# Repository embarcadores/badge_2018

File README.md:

= Crachá 2018 =

Proposta inicial

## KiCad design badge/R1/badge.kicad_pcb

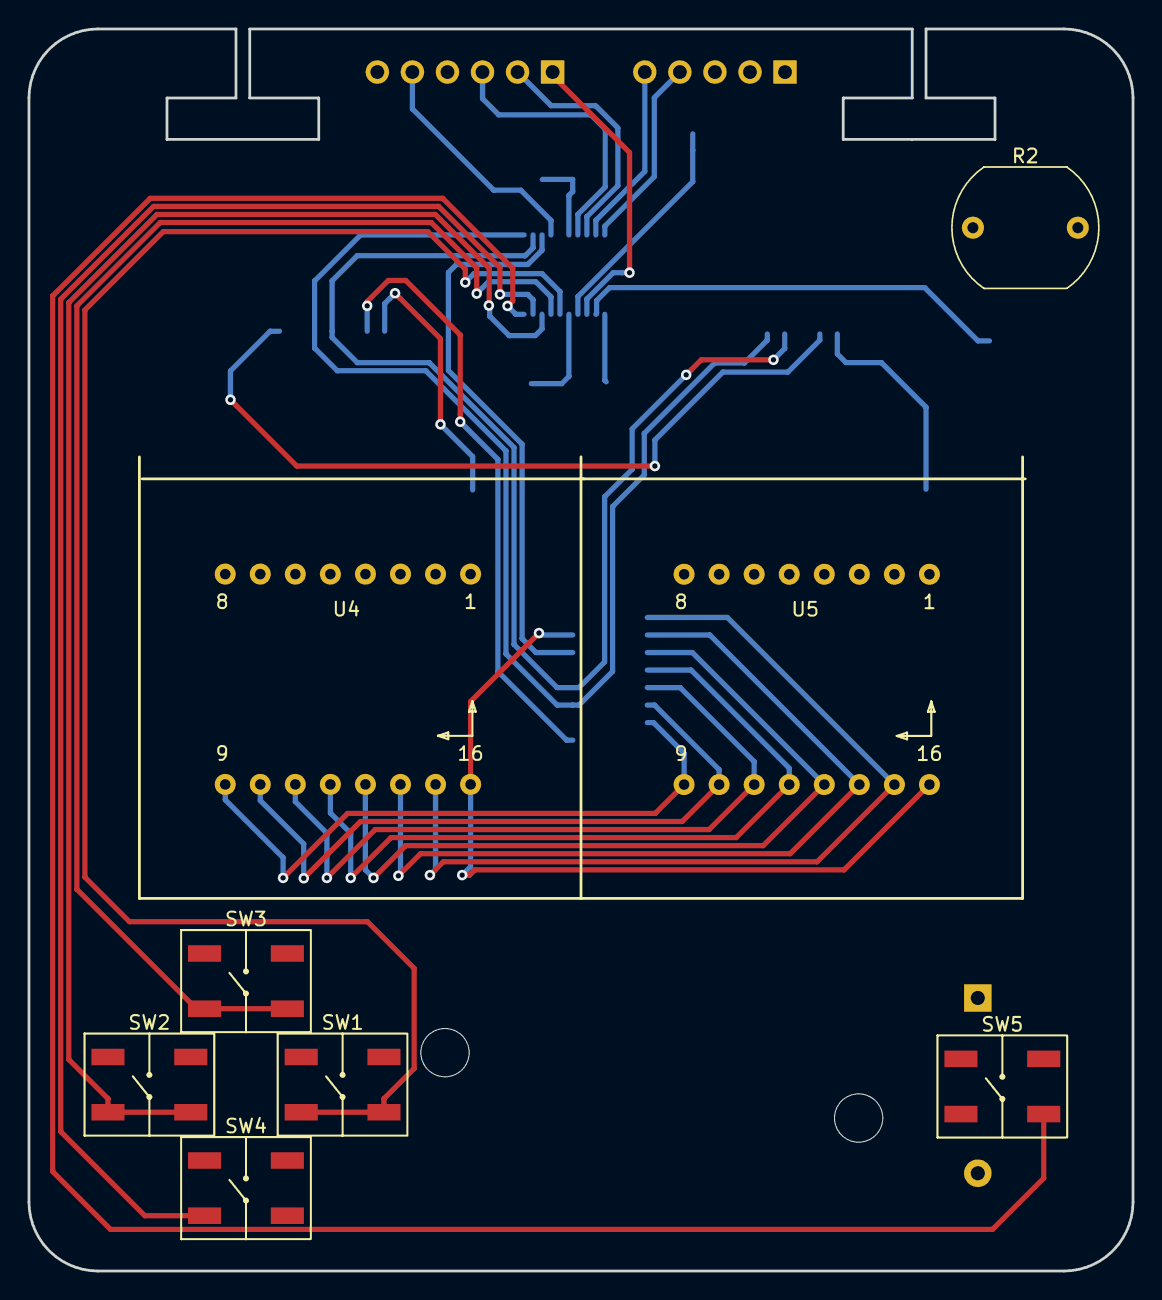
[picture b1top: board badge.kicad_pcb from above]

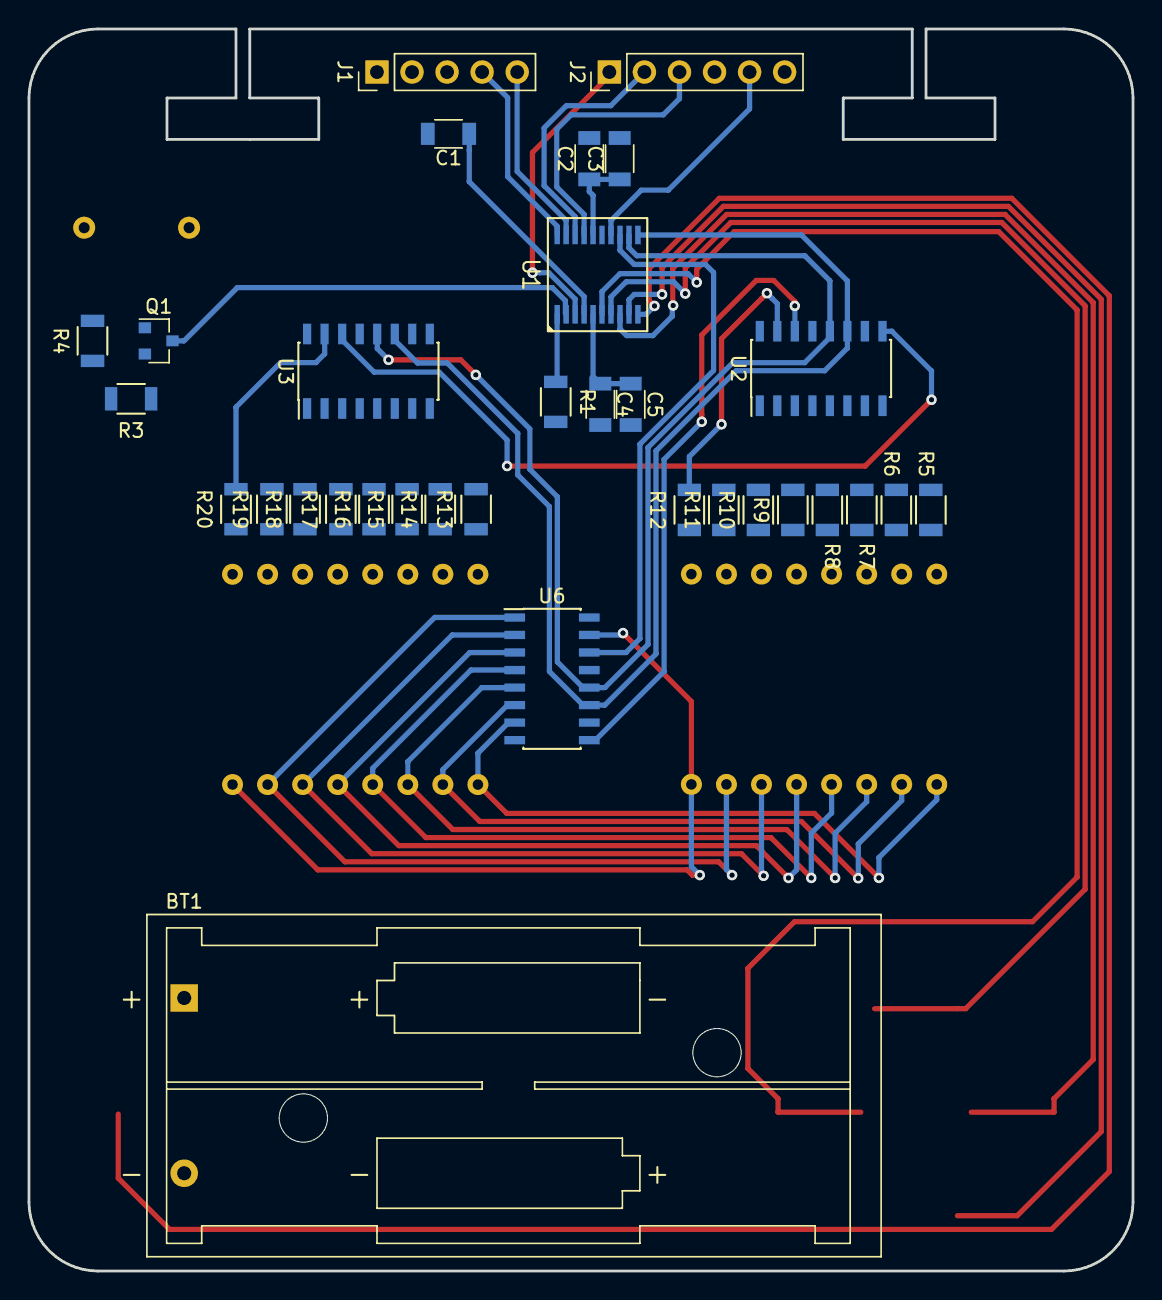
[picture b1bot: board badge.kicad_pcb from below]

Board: 2 copper layers, 80.0 x 90.0 mm, 40 parts (32 on the bottom side), 62 nets.

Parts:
BT1: AA; Keystone_2468_2xAAA
C1, C2: 100nF; C_1206
C3: 4.7uF; C_1206
C4: 10nF; C_1206
C5: 1uF; C_1206
J1: SWD; Pin_Header_Straight_1x05_Pitch2.54mm
J2: Conn_01x06; Pin_Header_Straight_1x06_Pitch2.54mm
Q1: NMOS_GSD; SOT-23
R1: 10K; R_1206_CUSTOM
R2: LDR03; Resistor_LDR_10x8.5_RM7.6
R3: 4k7; R_1206_CUSTOM
R4: 200R; R_1206_CUSTOM
R5, R6, R7, R8, R9, R10, R11, R12, R13, R14, R15, R16, R17, R18, R19, R20: 330R; R_1206_CUSTOM
SW1, SW2, SW3, SW4, SW5: SW_SPST; EVQ-Q2B02W
U1: STM32F030F4; TSOP-20-STM32F030F4
U2, U3, U6: 74HC595; SOIC-16_3.9x9.9mm_Pitch1.27mm
U4, U5: LEDMX; LED_8x8_1.9MM_20x20MM_Horiz

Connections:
/GPIO0: J2.1, U1.3
/HOLD: U1.12, U2.12, U3.12, U6.12
/MOSI: U1.13, U6.14
/NRST: C1.1, J1.3, U1.4
/RXD: Q1.3, R3.1, U1.2
/SCK: U1.11, U2.11, U3.11, U6.11
/SWCLK: J1.5, U1.19
/SWDIO: J1.4, U1.20
/SWDOWN: SW4.2, U1.9
/SWLEFT: SW2.2, U1.8
/SWMENU: SW5.2, U1.10
/SWRIGHT: SW1.2, U1.6
/SWTOP: SW3.2, U1.7
/UART_RX: J2.2, U1.18
/UART_TX: J2.3, U1.17
GND: BT1.2, C1.2, C2.2, C3.2, C4.2, C5.2, J1.2, J2.6, Q1.2, R1.2, R4.1, SW1.1, SW2.1, SW3.1, SW4.1, SW5.1, U1.15, U2.8, U2.13, U3.8, U3.13, U6.8, U6.13
unnamed: J2.5, U1.14
unnamed: Q1.1, R2.2, R4.2
unnamed: R1.1, U1.1
unnamed: R5.1, U4.8
unnamed: R5.2, U2.7
unnamed: R6.1, U4.7
unnamed: R6.2, U2.6
unnamed: R7.1, U4.6
unnamed: R7.2, U2.5
unnamed: R8.1, U4.5
unnamed: R8.2, U2.4
unnamed: R9.1, U4.4
unnamed: R9.2, U2.3
unnamed: R10.1, U4.3
unnamed: R10.2, U2.2
unnamed: R11.1, U4.2
unnamed: R11.2, U2.1
unnamed: R12.1, U4.1
unnamed: R12.2, U2.15
unnamed: R13.1, U5.8
unnamed: R13.2, U3.7
unnamed: R14.1, U5.7
unnamed: R14.2, U3.6
unnamed: R15.1, U5.6
unnamed: R15.2, U3.5
unnamed: R16.1, U5.5
unnamed: R16.2, U3.4
unnamed: R17.1, U5.4
unnamed: R17.2, U3.3
unnamed: R18.1, U5.3
unnamed: R18.2, U3.2
unnamed: R19.1, U5.2
unnamed: R19.2, U3.1
unnamed: R20.1, U5.1
unnamed: R20.2, U3.15
unnamed: U2.9, U3.14
unnamed: U2.14, U6.9
unnamed: U4.9, U5.9, U6.7
unnamed: U4.10, U5.10, U6.6
unnamed: U4.11, U5.11, U6.5
unnamed: U4.12, U5.12, U6.4
unnamed: U4.13, U5.13, U6.3
unnamed: U4.14, U5.14, U6.2
unnamed: U4.15, U5.15, U6.1
unnamed: U4.16, U5.16, U6.15
VCC: BT1.1, C2.1, C3.1, C4.1, C5.1, J1.1, J2.4, R2.1, R3.2, U1.5, U1.16, U2.10, U2.16, U3.10, U3.16, U6.10, U6.16

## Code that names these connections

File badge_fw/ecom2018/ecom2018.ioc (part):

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Mcu.Name=STM32F030F4Px
Mcu.Package=TSSOP20
Mcu.UserName=STM32F030F4Px
PA0.GPIOParameters=GPIO_Label
PA0.GPIO_Label=SWRIGHT
PA0.Signal=GPIO_Output
PA1.GPIOParameters=GPIO_Label
PA1.GPIO_Label=SWLEFT
PA1.Signal=GPIO_Output
PA10.GPIOParameters=GPIO_Label
PA10.GPIO_Label=USART_RX
PA10.Mode=Asynchronous
PA10.Signal=USART1_RX
PA13.Mode=Serial_Wire
PA13.Signal=SYS_SWDIO
PA14.Mode=Serial_Wire
PA14.Signal=SYS_SWCLK
PA2.GPIOParameters=GPIO_Label
PA2.GPIO_Label=SWDOWN
PA2.Signal=GPIO_Output
PA3.GPIOParameters=GPIO_Label
PA3.GPIO_Label=SWUP
PA3.Signal=GPIO_Output
PA4.GPIOParameters=GPIO_Label
PA4.GPIO_Label=SWMENU
PA4.Signal=GPIO_Output
PA5.GPIOParameters=GPIO_Label
PA5.GPIO_Label=DSP_SCK
PA5.Mode=TX_Only_Simplex_Unidirect_Master
PA5.Signal=SPI1_SCK
PA6.GPIOParameters=GPIO_Label
PA6.GPIO_Label=DSP_HOLD
PA6.Signal=GPIO_Output
PA7.GPIOParameters=GPIO_Label
PA7.GPIO_Label=DSP_MOSI
PA7.Mode=TX_Only_Simplex_Unidirect_Master
PA7.Signal=SPI1_MOSI
PA9.GPIOParameters=GPIO_Label
PA9.GPIO_Label=USART_TX
PA9.Mode=Asynchronous
PA9.Signal=USART1_TX
PB1.GPIOParameters=GPIO_Label
PB1.GPIO_Label=ADC_PWM
PB1.Mode=IN9
PB1.Signal=ADC_IN9
PF0-OSC_IN.GPIOParameters=GPIO_Label
PF0-OSC_IN.GPIO_Label=RXD
PF0-OSC_IN.Signal=GPIO_Input
PF1-OSC_OUT.GPIOParameters=GPIO_Label
PF1-OSC_OUT.GPIO_Label=TXD
PF1-OSC_OUT.Signal=GPIO_Output
board=ecom2018

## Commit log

2018-03-02 First version
2018-03-02 some de mo images

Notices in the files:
badge/R1/badge.kicad_pcb:
All rights reserved
